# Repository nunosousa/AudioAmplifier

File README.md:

# AudioAmplifier

An in-development hardware design for a stereo-plus-subwoofer (2.1) audio
amplifier. The design is centered on an ADAU1701 SigmaDSP, with TPA3116D2
Class-D power-amplifier stages.

> **Status: work in progress.** The current schematics describe an architectural
> transition to DSP-based processing; the DSP circuit is not yet wired or ready
> for fabrication. The PCB, simulation, and exported schematic PDF are also
> incomplete or out of date. See [Design status](docs/DESIGN_STATUS.md) before
> relying on any design files.

## Intended signal path

```text
Stereo line inputs
    → analog input conditioning
    → ADAU1701 ADCs
    → DSP volume, bass/treble EQ, and 2.1 crossover
    → three DAC channels and output conditioning
    → stereo and mono TPA3116D2 stages
    → left, right, and subwoofer outputs
```

The preamp is intended to provide input conditioning only. User-adjustable
volume, bass, treble, and crossover functions are intended to run in the DSP.
The current front-panel concept uses an RP2350, a 2.4-inch 320 × 240 colour
display, one main encoder, and dedicated parameter/display/mute buttons. The
display is a context-sensitive instrumentation UI, not a menu system; see the
[front-panel specification](docs/FRONT_PANEL.md) and
[UI firmware architecture](docs/UI_FIRMWARE_ARCHITECTURE.md).

## Open the design

Open [`electronics/audio-amplifier/AudioAmplifier.kicad_pro`](electronics/audio-amplifier/AudioAmplifier.kicad_pro)
in **KiCad 10 or a compatible version**. The project includes a project-local
symbol library table; its custom amplifier symbols are in
[`Amplifier_Audio_custom.kicad_sym`](electronics/audio-amplifier/Amplifier_Audio_custom.kicad_sym).

The SigmaStudio project and its generated artifacts are in
[`electronics/audio-amplifier/dsp/`](electronics/audio-amplifier/dsp/). The
LTspice audio-path file is in
[`electronics/audio-amplifier/simulation/LTspice/`](electronics/audio-amplifier/simulation/LTspice/).
Neither folder currently provides a verified end-to-end validation of the
latest schematic.

## Repository map

| Path | Contents |
| --- | --- |
| [`electronics/audio-amplifier/`](electronics/audio-amplifier/) | Main 2.1 KiCad project |
| `AudioAmplifier.kicad_sch` | Top-level sheet hierarchy and signal interfaces |
| `dsp.kicad_sch` | ADAU1701 symbol and proposed DSP I/O sheet |
| `preamplifier.kicad_sch` | Analog input-stage design, intended to be reduced to input conditioning |
| `stereo_amp.kicad_sch`, `mono_amp.kicad_sch` | TPA3116D2 power-amplifier stages |
| `power.kicad_sch`, `control.kicad_sch` | Power and amplifier mute/control circuits |
| `crossover.kicad_sch` | Standalone analog crossover design retained as a reference; not in the current top-level hierarchy |
| `dsp/` | ADAU1701 SigmaStudio project, compiler outputs, and generated program data |
| `simulation/` | Filter-design spreadsheet and LTspice files |
| [`electronics/datasheets/`](electronics/datasheets/) | Component reference material |
| [`mechanical/enclosure/`](mechanical/enclosure/) | Enclosure CAD source, exchange exports, and drawings |
| [`firmware/`](firmware/) | MCU firmware, shared code, and development tools |

## Current validation

- **KiCad ERC/DRC:** not yet run on the current design.
- **PCB:** currently reset for redesign; it has no placed footprints or routed copper.
- **LTspice:** `Audio_path.asc` currently contains only the LTspice file header.
- **DSP:** committed SigmaStudio outputs exist, but have not been verified against
  the current DSP schematic and intended signal path.
- **PDF:** `AudioAmplifier.pdf` predates the latest schematic changes; treat it
  as stale until regenerated.

See [docs/DESIGN_STATUS.md](docs/DESIGN_STATUS.md) for known gaps, open
engineering decisions, and a suggested completion sequence.
For a pin-by-pin checklist of the DSP hardware to complete, see
[docs/ADAU1701_INTEGRATION.md](docs/ADAU1701_INTEGRATION.md).

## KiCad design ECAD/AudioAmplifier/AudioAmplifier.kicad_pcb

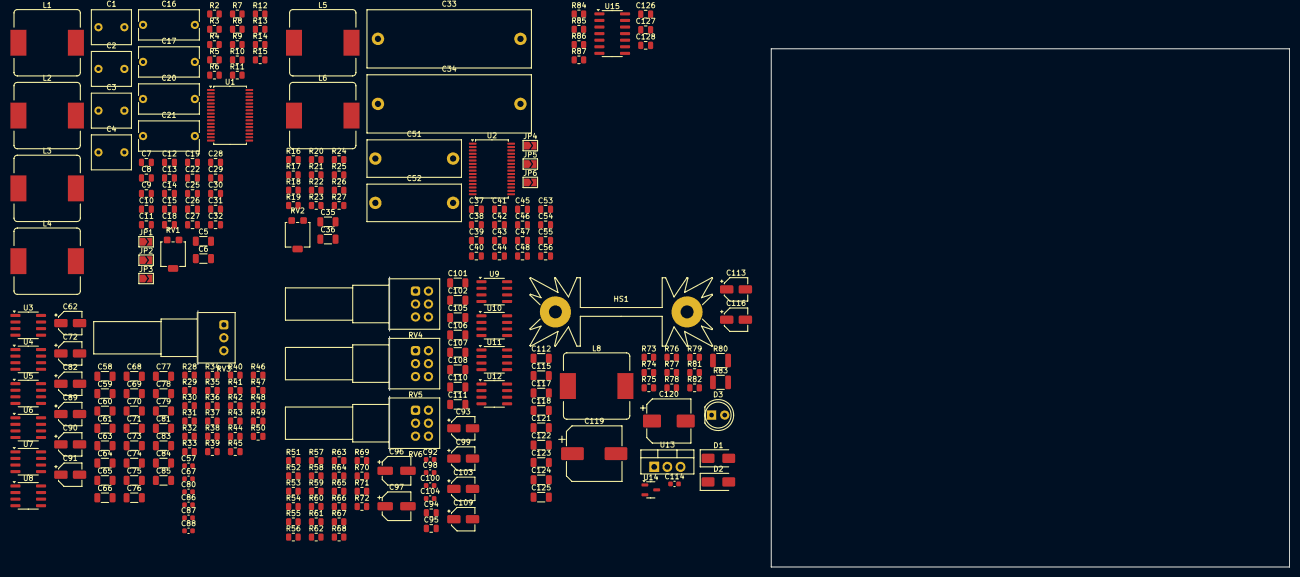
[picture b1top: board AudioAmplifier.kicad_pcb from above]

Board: 2 copper layers, 248 parts (0 on the bottom side), 137 nets, no tracks yet.

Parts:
C1, C2, C3, C4: 1u5C; C_Rect_L7.5mm_W6.5mm_P5.00mm
C5, C6, C35, C36, C122: 1uC; C_1206_3216Metric
C7, C8, C25, C26, C27, C28, C37, C38, C53, C54, C94, C95: 1nC; C_0805_2012Metric
C9, C10, C11, C12, C39, C40, C41, C42: 220nC; C_0805_2012Metric
C13, C14, C43, C44, C128: 100nC; C_0805_2012Metric
C15, C18, C19, C22, C45, C46, C47, C48: 330pC; C_0805_2012Metric
C16, C17, C20, C21: 680nC; C_Rect_L11.5mm_W5.6mm_P10.00mm_MKT
C29, C30, C31, C32, C55, C56: 10nC; C_0805_2012Metric
C33, C34: 3u3C; C_Rect_L31.5mm_W11.0mm_P27.50mm_MKS4
C51, C52: 1uC; C_Rect_L18.0mm_W7.0mm_P15.00mm_FKS3_FKP3
C57, C67, C80, C86, C87, C88, C92, C98, C100, C104, C114: 100nC; C_0603_1608Metric
C58, C59, C60, C61, C63, C64, C65, C66, C68, C69, C70, C71, C74, C75, C76, C77, C78, C79, C81, C83, C84, C85, C101, C102, C112, C123: 100nC; C_1206_3216Metric
C62, C72, C82, C89, C90, C91, C93, C99, C103, C109, C113, C116: 10uC; CP_Elec_4x5.4
C73, C110, C111: 100pC; C_1206_3216Metric
C96, C97: 22uC; CP_Elec_5x5.4
C105, C106, C107, C108: 15nC; C_1206_3216Metric
C115, C117, C118, C121: 10uC; C_1206_3216Metric
C119: 1000uC; CP_Elec_10x10.5
C120: 100uC; CP_Elec_8x10
C124: 10nC; C_1206_3216Metric
C125: 1nC; C_1206_3216Metric
C126, C127: C; C_0805_2012Metric
D1, D2: S1A-13-F; D_SMA
D3: LED; LED_D5.0mm
HS1: Heatsink; Heatsink_Fischer_SK104-STC-STIC_35x13mm_2xDrill2.5mm
JP1, JP2, JP3, JP4, JP5, JP6: SolderJumper_2_Open; SolderJumper-2_P1.3mm_Open_TrianglePad1.0x1.5mm
L1, L2, L3, L4, L5, L6, L8: 10uL; L_TaiTech_TMPC1265_13.5x12.5mm
R2, R3, R4, R16, R17, R18, R55, R56: 100kR; R_0805_2012Metric
R5, R19: 20kR; R_0805_2012Metric
R6, R84, R85, R86, R87: R; R_0805_2012Metric
R7: 5k6R; R_0805_2012Metric
R8, R9, R10, R11, R22, R23, R24, R25: 10R; R_0805_2012Metric
R12, R13, R14, R15, R26, R27: 3R3; R_0805_2012Metric
R20: 47kR; R_0805_2012Metric
R21: 75kR; R_0805_2012Metric
R28, R29, R30, R31, R32, R36, R37, R43, R44, R45, R46, R49, R50: 5kR; R_0805_2012Metric
R33, R34, R39, R40, R41, R42, R47, R48, R81, R82: 10kR; R_0805_2012Metric
R35, R69, R70: 680R; R_0805_2012Metric
R38, R71, R72: 4k7R; R_0805_2012Metric
R51, R52, R76: 100R; R_0805_2012Metric
R53, R54: 220kR; R_0805_2012Metric
R57, R58, R59, R60: 1k8R; R_0805_2012Metric
R61, R62: 12kR; R_0805_2012Metric
R63, R64, R65, R66, R67, R68, R74, R79: 1kR; R_0805_2012Metric
R73, R77: 374R; R_0805_2012Metric
R75: 1500R; R_0805_2012Metric
R78: 240R; R_0805_2012Metric
R80: 100kR; R_1210_3225Metric
R83: 1kR; R_1210_3225Metric
RV1, RV2: 100kR; Potentiometer_Bourns_3314G_Vertical
RV3: 10kR; Potentiometer_Alps_RK097_Single_Horizontal
RV4, RV5, RV6: 10kR; Potentiometer_Alps_RK097_Dual_Horizontal
U1, U2: TPA3116D2DAD; TSSOP-32_6.1x11mm_P0.65mm
U3, U4, U5, U6, U7, U8, U9, U10, U11, U12: OPA1656; SOIC-8_3.9x4.9mm_P1.27mm
U13: LM317_TO-220; TO-220-3_Vertical
U14: LM4041LP-ADJ; SOT-23-3
U15: HEF4093B; SO-14_3.9x8.65mm_P1.27mm

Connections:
+4V5: C81.2, C85.2, C114.1, C116.1, R33.2, R34.2, R39.2, R40.2, R55.2, R56.2, R73.1, R77.2, R79.1, U3.5 (+), U5.5 (+), U7.3 (+), U7.5 (+), U8.5 (+), U10.3 (+), U10.5 (+), U12.3 (+), U12.5 (+), U14.2 (K)
+9V: C57.1, C62.1, C67.1, C72.1, C80.1, C82.1, C86.1, C87.1, C88.1, C89.1, C90.1, C91.1, C92.1, C93.1, C98.1, C99.1, C100.1, C103.1, C104.1, C109.1, C117.1, C118.1, D1.2 (A), D2.1 (K), R76.1, R78.1, U3.8 (V+), U4.8 (V+), U5.8 (V+), U6.8 (V+), U7.8 (V+), U8.8 (V+), U9.8 (V+), U10.8 (V+), U11.8 (V+), U12.8 (V+), U13.2 (VO)
+12V: C119.1, C120.1, C121.1, C122.1, C123.1, C124.1, C125.1, L8.2, R80.1, R82.1, R84.1, R85.1
/Control/MUTE: U1.12 (MUTE), U2.12 (MUTE), U15.10
/Control/PWR_ON: R81.1, U1.2 (~SDZ), U2.2 (~SDZ), U15.4
/Control/~FAULTZ: U1.3 (~FAULTZ), U2.3 (~FAULTZ), U15.1
/Crossover/IN_LEFT: C58.1, C59.1, C110.2, R28.2, R71.2, RV6.1, U12.1
/Crossover/IN_RIGHT: C60.1, C61.1, C111.2, R29.2, R72.2, RV6.4, U12.7
/Crossover/OUT_HIGH_N_LEFT: C4.1, R45.2, U7.7
/Crossover/OUT_HIGH_N_RIGHT: C2.1, R46.2, U7.1
/Crossover/OUT_HIGH_P_LEFT: C3.1, R36.2, R43.1, U6.6 (-), U6.7
/Crossover/OUT_HIGH_P_RIGHT: C1.1, R37.2, R44.1, U5.1, U5.2 (-)
/Crossover/OUT_LOW_N: C34.1, R50.2, U8.7
/Crossover/OUT_LOW_P: C33.1, C83.1, C84.2, R49.1, U8.1, U8.2 (-)
/Mono Amplifier/AM0: JP6.2 (B), R18.2, U2.15 (AM0)
/Mono Amplifier/AM1: JP5.2 (B), R17.2, U2.14 (AM1)
/Mono Amplifier/AM2: JP4.2 (B), R16.2, U2.13 (AM2)
/Mono Amplifier/OUT_N_SUB: C52.2, C54.2, L6.1, R27.2
/Mono Amplifier/OUT_P_SUB: C51.1, C53.1, L5.2, R26.1
/Mono Amplifier/SYNC: U1.16 (SYNC), U2.16 (SYNC)
/Stereo Amplifier/AM0: JP3.2 (B), R4.2, U1.15 (AM0)
/Stereo Amplifier/AM1: JP2.2 (B), R3.2, U1.14 (AM1)
/Stereo Amplifier/AM2: JP1.2 (B), R2.2, U1.13 (AM2)
/Stereo Amplifier/OUT_N_LEFT: C21.2, C28.2, L4.1, R15.2
/Stereo Amplifier/OUT_N_RIGHT: C17.2, C26.2, L2.1, R13.2
/Stereo Amplifier/OUT_P_LEFT: C20.1, C27.1, L3.2, R14.1
/Stereo Amplifier/OUT_P_RIGHT: C16.1, C25.1, L1.2, R12.1
GND: C5.2, C6.2, C7.2, C8.2, C13.2, C14.2, C16.2, C17.1, C20.2, C21.1, C25.2, C26.1, C27.2, C28.1, C29.2, C30.1, C31.2, C32.1, C35.2, C36.2, C37.2, C38.2, C43.2, C44.2, C51.2, C52.1, C53.2, C54.1, C55.2, C56.1, C57.2, C62.2, C67.2, C72.2, C80.2, C82.2, C86.2, C87.2, C88.2, C89.2, C90.2, C91.2, C92.2, C93.2, C94.2, C95.2, C98.2, C99.2, C100.2, C103.2, C104.2, C109.2, C112.2, C113.2, C114.2, C115.2, C116.2, C117.2, C118.2, C119.2, C120.2, C121.2, C122.2, C123.2, C124.2, C125.2, C126.2, C127.2, C128.2, D3.1 (K), JP1.1 (A), JP2.1 (A), JP3.1 (A), JP4.1 (A), JP5.1 (A), JP6.1 (A), R5.2, R7.2, R8.2, R9.2, R10.2, R11.2, R19.2, R21.2, R22.2, R23.2, R24.2, R25.2, R53.2, R54.2, R74.2, R75.2, R79.2, R80.2, U1.1 (MODSEL), U1.9 (GND), U1.22 (GND), U1.25 (GND), U1.28 (GND), U2.1 (MODSEL), U2.9 (GND), U2.10 (LINP), U2.11 (LINN), U2.22 (GND), U2.25 (GND), U2.28 (GND), U3.4 (V-), U4.4 (V-), U5.4 (V-), U6.4 (V-), U7.4 (V-), U8.4 (V-), U9.4 (V-), U10.4 (V-), U11.4 (V-), U12.4 (V-), U14.3 (A), U15.7 (GND)
unnamed: C15.2, R8.1
unnamed: C18.2, R9.1
unnamed: C19.2, R10.1
unnamed: C22.2, R11.1
unnamed: C29.1, R12.2
unnamed: C30.2, R13.1
unnamed: C31.1, R14.2
unnamed: C32.2, R15.1
unnamed: C45.2, R22.1
unnamed: C46.2, R23.1
unnamed: C47.2, R24.1
unnamed: C48.2, R25.1
unnamed: C55.1, R26.2
unnamed: C56.2, R27.1
unnamed: C58.2, C59.2, C63.1, C64.1, R31.1
unnamed: C60.2, C61.2, C65.1, C66.1, R32.1
unnamed: C68.2, C69.2, C74.1, C75.1, R36.1
unnamed: C70.2, C71.2, C76.1, C77.1, R37.1
unnamed: C73.2, R38.2, R41.1, RV3.1, U5.7
unnamed: C78.2, C79.1, R41.2, R42.1
unnamed: C83.2, C84.1, R47.2, R48.1
unnamed: C94.1, C96.2, R51.2, R53.1
unnamed: C95.1, C97.2, R52.2, R54.1
unnamed: C101.1, R57.2, RV4.1
unnamed: C101.2, R58.1, RV4.3
unnamed: C102.1, R59.2, RV4.4
unnamed: C102.2, R60.1, RV4.6
unnamed: C105.1, R65.2
unnamed: C105.2, RV5.1
unnamed: C106.1, RV5.3
unnamed: C106.2, R66.1
unnamed: C107.1, R67.2
unnamed: C107.2, RV5.4
unnamed: C108.1, RV5.6
unnamed: C108.2, R68.1
unnamed: C113.1, R76.2, R77.1
unnamed: C115.1, D2.2 (A), R75.1, R78.2, U13.1 (ADJ)
unnamed: D3.2 (A), R83.2
unnamed: R84.2, R86.1
unnamed: C126.1, R86.2, U15.8, U15.9
unnamed: R85.2, R87.1
unnamed: C127.1, R87.2, U15.12, U15.13
unnamed: R5.1, RV1.3
unnamed: R19.1, RV2.3
unnamed: R30.1, RV3.3, U3.7
unnamed: R57.1, R65.1, RV6.3, U10.1
unnamed: R59.1, R67.1, RV6.6, U10.7
unnamed: R61.1, RV4.2
unnamed: R62.1, RV4.5
unnamed: R63.2, RV5.2
unnamed: R64.2, RV5.5
unnamed: C12.2, U1.20 (BSNL)
unnamed: C10.2, U1.26 (BSNR)
unnamed: C11.2, U1.24 (BSPL)
unnamed: C9.1, U1.30 (BSPR)
unnamed: R6.2, R7.1, U1.8 (GAIN_SLV)
unnamed: C6.1, R6.1, RV1.1, U1.7 (GVDD)
unnamed: C4.2, U1.11 (LINN)
unnamed: C3.2, U1.10 (LINP)
unnamed: C12.1, C22.1, L4.2, U1.21 (OUTNL)
unnamed: C10.1, C18.1, L2.2, U1.27 (OUTNR)
unnamed: C11.1, C19.1, L3.1, U1.23 (OUTPL)
unnamed: C9.2, C15.1, L1.1, U1.29 (OUTPR)
unnamed: C5.1, RV1.2, U1.6 (PLIMIT)
unnamed: C2.2, U1.5 (RINN)
unnamed: C1.2, U1.4 (RINP)
unnamed: C42.2, U2.20 (BSNL)
unnamed: C40.2, U2.26 (BSNR)
unnamed: C41.2, U2.24 (BSPL)
unnamed: C39.1, U2.30 (BSPR)
unnamed: R20.2, R21.1, U2.8 (GAIN_SLV)
unnamed: C36.1, R20.1, RV2.1, U2.7 (GVDD)
unnamed: C41.1, C42.1, C47.1, C48.1, L6.2, U2.21 (OUTNL), U2.23 (OUTPL)
unnamed: C39.2, C40.1, C45.1, C46.1, L5.1, U2.27 (OUTNR), U2.29 (OUTPR)
unnamed: C35.1, RV2.2, U2.6 (PLIMIT)
unnamed: C34.2, U2.5 (RINN)
unnamed: C33.2, U2.4 (RINP)
unnamed: C65.2, C66.2, R34.1, U3.3 (+)
unnamed: C70.1, C71.1, R32.2, U3.1, U3.2 (-)
unnamed: R28.1, R29.1, R30.2, U3.6 (-)
unnamed: RV3.2, U4.3 (+)
unnamed: R35.1, U4.1, U4.2 (-)
unnamed: C63.2, C64.2, R33.1, U4.5 (+)
unnamed: C68.1, C69.1, R31.2, U4.6 (-), U4.7
unnamed: C76.2, C77.2, R40.1, U5.3 (+)
unnamed: C73.1, R35.2, R38.1, U5.6 (-)
unnamed: C81.1, R42.2, U6.3 (+)
unnamed: C78.1, C79.2, R47.1, U6.1, U6.2 (-)
unnamed: C74.2, C75.2, R39.1, U6.5 (+)
unnamed: R44.2, R46.1, U7.2 (-)
unnamed: R43.2, R45.1, U7.6 (-)
unnamed: C85.1, R48.2, U8.3 (+)
unnamed: R49.2, R50.1, U8.6 (-)
unnamed: C96.1, R55.1, U9.3 (+)
unnamed: R58.2, R66.2, U9.1, U9.2 (-)
unnamed: C97.1, R56.1, U9.5 (+)
unnamed: R60.2, R68.2, U9.6 (-), U9.7
unnamed: R61.2, R63.1, U10.2 (-)
unnamed: R62.2, R64.1, U10.6 (-)
unnamed: RV6.2, U11.3 (+)
unnamed: R69.1, U11.1, U11.2 (-)
unnamed: RV6.5, U11.5 (+)
unnamed: R70.1, U11.6 (-), U11.7
unnamed: C110.1, R69.2, R71.1, U12.2 (-)
unnamed: C111.1, R70.2, R72.1, U12.6 (-)
unnamed: R73.2, R74.1, U14.1 (FB)
unnamed: U15.3, U15.5, U15.6
unnamed: U15.2, U15.11
PVCC: C7.1, C8.1, C13.1, C14.1, C37.1, C38.1, C43.1, C44.1, C112.1, C128.1, D1.1 (K), R2.1, R3.1, R4.1, R16.1, R17.1, R18.1, R83.1, U1.17 (AVCC), U1.18 (PVCC), U1.19 (PVCC), U1.31 (PVCC), U1.32 (PVCC), U2.17 (AVCC), U2.18 (PVCC), U2.19 (PVCC), U2.31 (PVCC), U2.32 (PVCC), U13.3 (VI), U15.14 (VCC)

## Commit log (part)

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2024-03-16 Progressed ECAD.
2024-04-14 Progressed ECAD
2025-03-22 Added DSP.
2025-03-22 Updated DSP.
